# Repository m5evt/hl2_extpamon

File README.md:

# hl2_extpamon

## Overview

Power amplifier instrumentation board designed to couple to the Hermes-Lite2 SDR. 

The firmware/hardware is designed to couple to an LM35 temperature sensor.

The hardware should cope with upto 8 A of current to a power amplifer. However, at present the current is scaled to a full scale of 5 A. This can be changed in [hl2_extpamon.h](https://github.com/m5evt/hl2_extpamon/blob/main/firmware/hl2_extpamon.h). Other parameters such as automatic temperature turn on for the fan can be configured here.

The module uses an ATTINY414 device with an i2c address of 0x2A. 

## Reading data from device

Data can be read from the device over i2c by send the first data frame as 0x01.

For example, to read temperature and current from the device send:

```
07AA0100
```

This will return a 16 bit number comprised of the following bytes:

| Byte 3  | Byte 2 | Byte 1  | Byte 0 |
| ----------- | ----------- |----------- | ----------- |
| Device status      | PORTA status       |Current      | Temperature |

Temperature = e.g. 26 is 26 deg C

Current is scaled to a maximum current of 5 A represented in 255 bits. A return value of 128 = (128 / 255) * 5 = 2.51 A.

PORTA status corresponds to:

| Bit | Description |
|----------- | ----------- |
| 0 | Reserved |
| 1 | HL2 CN8 control |
| 2 | Enable PA power |
| 3 | FAN 1 |
| 4 | FAN 2 |
| 5 | N/a
| 6 | N/a
| 7 | Reserved |

Device status correspod to:

| Bit | Description |
|----------- | ----------- |
| 0 | Sampling ADC5 |
| 1 | Sampling ADC6 |

## Writing data to device

PORTA I/O can be set/clear by writing to address 0x02 in the device. For example, to enable the PA and turn on the fans send:

```
06AA021E
```

## Programming the ATTINY414

To program, the Makefile uses [pymcuprog](https://github.com/microchip-pic-avr-tools/pymcuprog) and UPDI. This does not require any specialist tools other than a TTL USB adapter and a resistor. See [here](https://github.com/mraardvark/pyupdi).

To program the device, from a command line run:
```
make clean && make erase && make program
```

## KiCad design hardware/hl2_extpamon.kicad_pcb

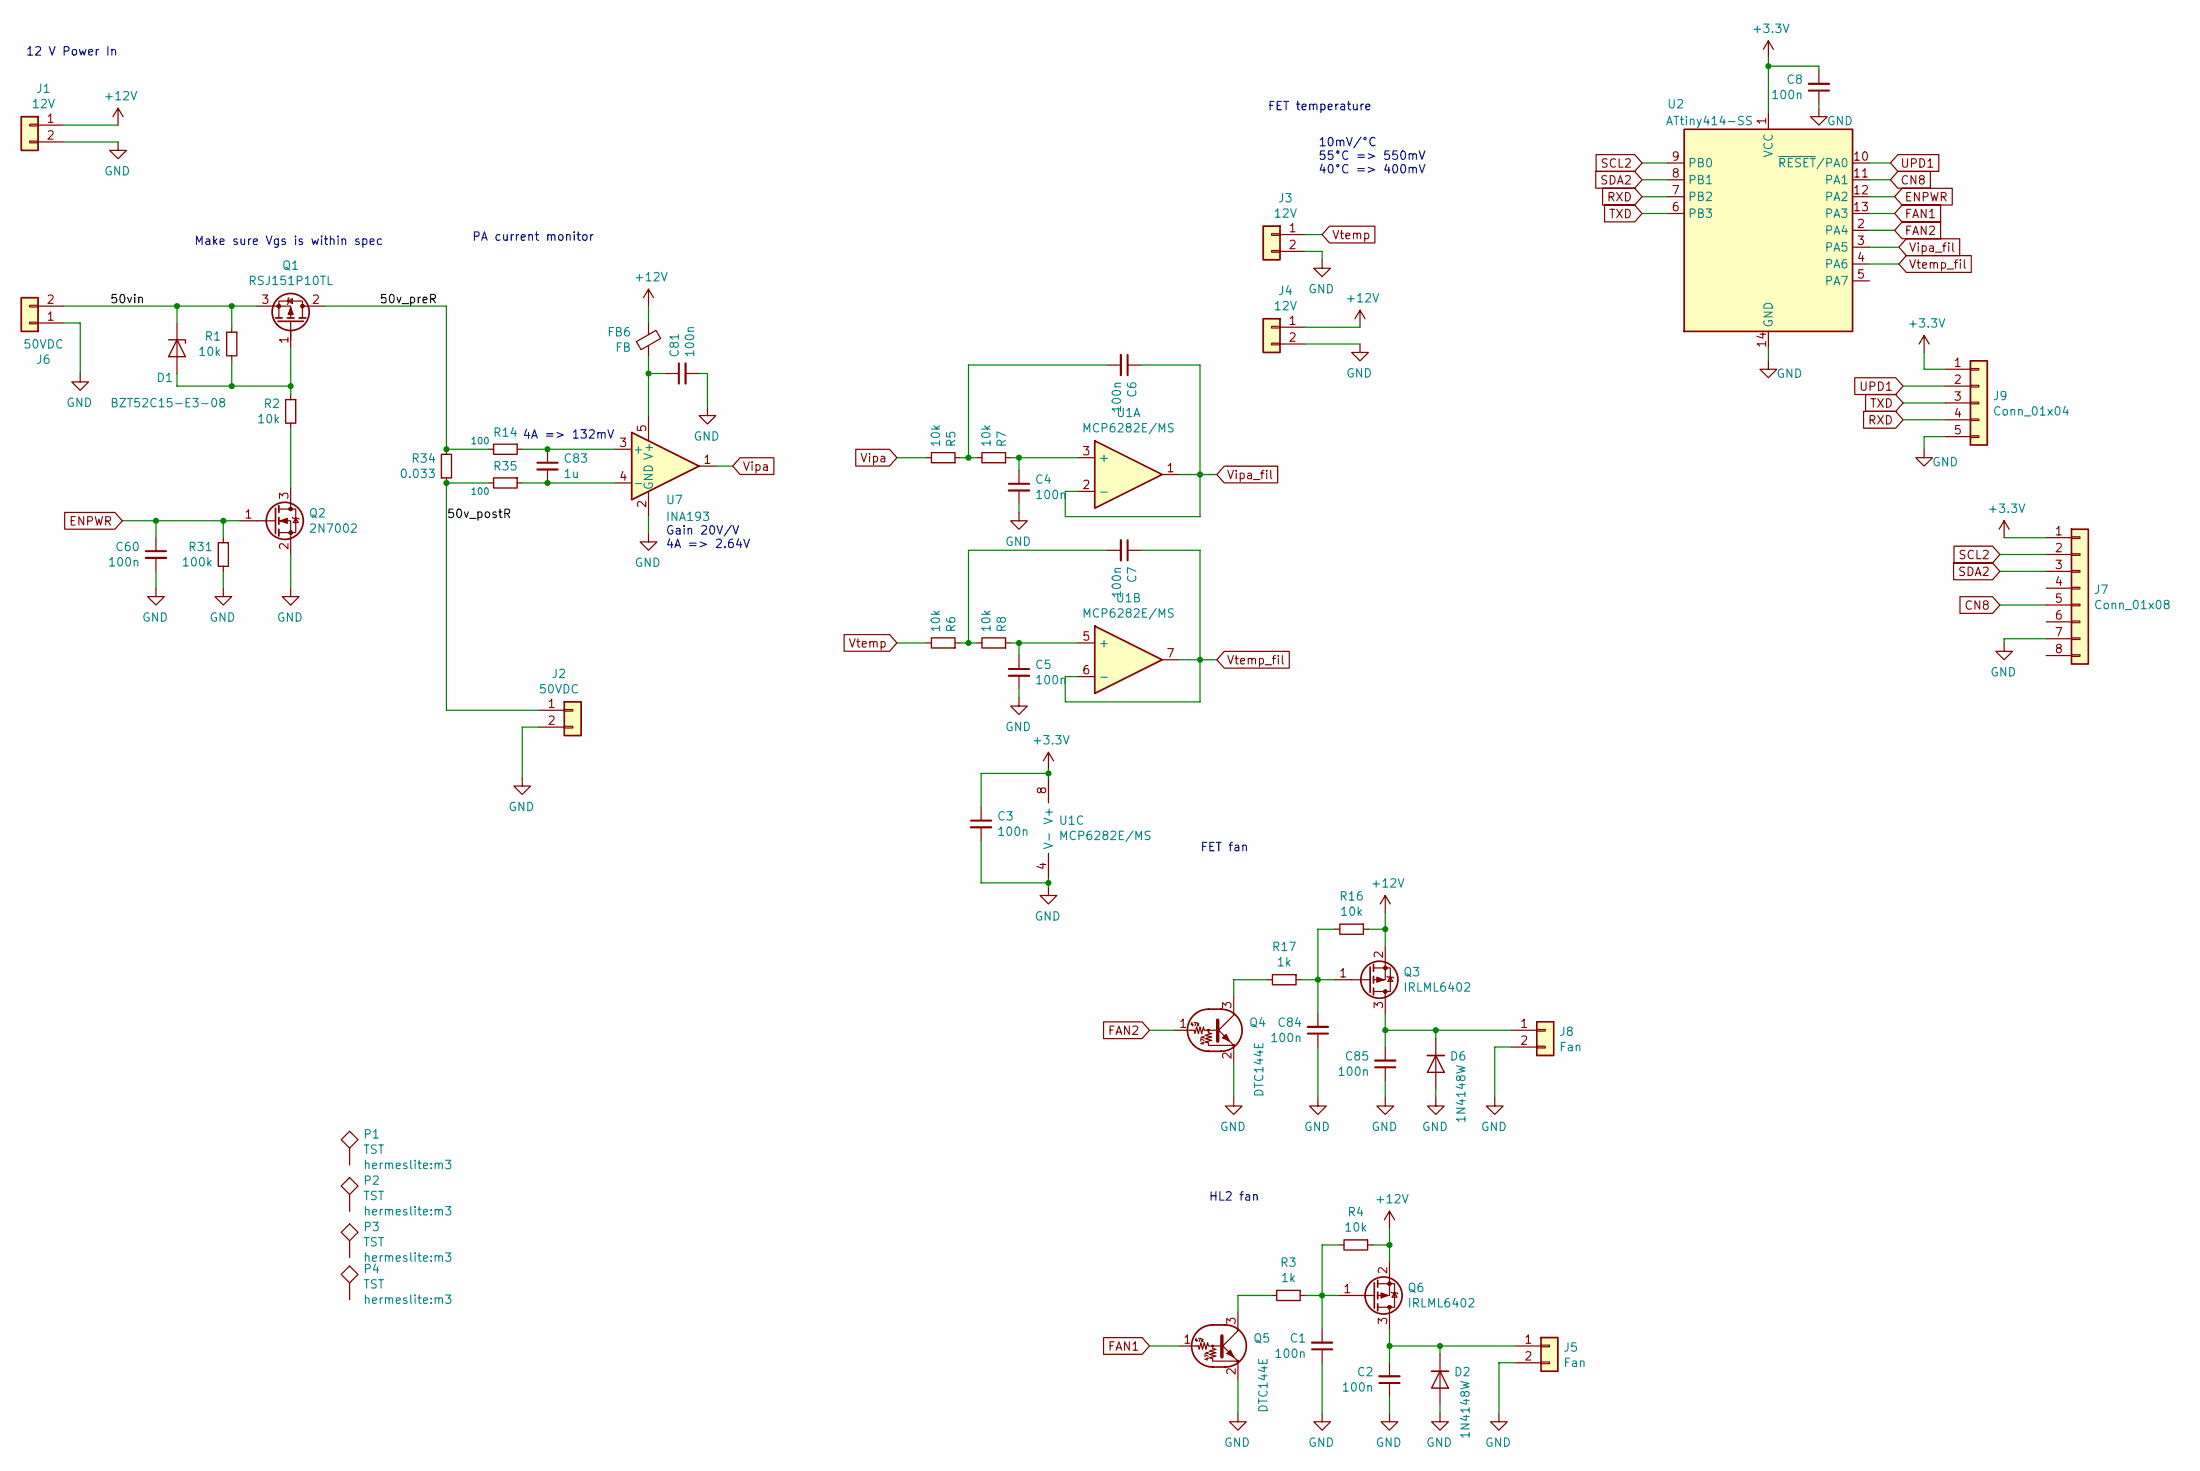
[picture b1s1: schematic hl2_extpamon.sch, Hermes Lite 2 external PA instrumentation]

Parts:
C1, C2, C3, C4, C5, C6, C7, C8, C60, C81, C84, C85: 100n; C_0603_1608Metric_Pad1.08x0.95mm_HandSolder
C83: 1u; C_0603_1608Metric_Pad1.08x0.95mm_HandSolder
D1: BZT52C15-E3-08; D_SOD-123
D2, D6: 1N4148W; D_SOD-123
FB6: FB; L_0805_2012Metric
J1, J3, J4: 12V; TerminalBlock_Phoenix_PT-1,5-2-3.5-H_1x02_P3.50mm_Horizontal
J2, J6: 50VDC; TerminalBlock_Phoenix_PT-1,5-2-5.0-H_1x02_P5.00mm_Horizontal
J5, J8: Fan; JST_XH_B2B-XH-A_1x02_P2.50mm_Vertical
J7: Conn_01x08; PinHeader_1x08_P2.54mm_Vertical
J9: Conn_01x04; PinHeader_1x05_P2.54mm_Vertical
P1, P2, P3, P4: TST; m3
Q1: RSJ151P10TL; TO-263-3_TabPin2
Q2: 2N7002; SOT-23
Q3, Q6: IRLML6402; SOT-23
Q4, Q5: DTC144E; SOT-23
R1, R2, R4, R5, R6, R7, R8, R16: 10k; R_0603_1608Metric_Pad0.98x0.95mm_HandSolder
R3, R17: 1k; R_0603_1608Metric_Pad0.98x0.95mm_HandSolder
R14, R35: 100; R_0603_1608Metric_Pad0.98x0.95mm_HandSolder
R31: 100k; R_0603_1608Metric_Pad0.98x0.95mm_HandSolder
R34: 0.033; rsense_1206wide
U1: MCP6282E/MS; MSOP-8_3x3mm_P0.65mm
U2: ATtiny414-SS; SOIC-14_3.9x8.7mm_P1.27mm
U7: INA193; SOT-23-5

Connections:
+3V3: C3.1, C8.2, J7.1, J9.1, U1.8 (V+), U2.1 (VCC)
+12V: FB6.2, J1.1, J4.1, Q3.2 (S), Q6.2 (S), R4.1, R16.1
/50v_postR: J2.1, R34.1, R35.2
/50v_preR: Q1.2 (D), R14.2, R34.2
/50vin: D1.1 (K), J6.2, Q1.3 (S), R1.1
CN8: J7.5, U2.11 (PA1)
ENPWR: C60.1, Q2.1 (G), R31.1, U2.12 (PA2)
FAN1: Q5.1 (B), U2.13 (PA3)
FAN2: Q4.1 (B), U2.2 (PA4)
GND: C1.1, C2.1, C3.2, C4.2, C5.2, C8.1, C60.2, C81.2, C84.1, C85.1, D2.2 (A), D6.2 (A), J1.2, J2.2, J3.2, J4.2, J5.2, J6.1, J7.7, J8.2, J9.5, Q2.2 (S), Q4.2 (E), Q5.2 (E), R31.2, U1.4 (V-), U2.14 (GND), U7.2 (GND)
unnamed: C1.2, Q6.1 (G), R3.1, R4.2
unnamed: C2.2, D2.1 (K), J5.1, Q6.3 (D)
unnamed: C4.1, R7.1, U1.3 (+)
unnamed: C5.1, R8.1, U1.5 (+)
unnamed: C6.2, R5.1, R7.2
unnamed: C7.2, R6.1, R8.2
unnamed: C81.1, FB6.1, U7.5 (V+)
unnamed: C83.1, R14.1, U7.3 (+)
unnamed: C83.2, R35.1, U7.4 (-)
unnamed: C84.2, Q3.1 (G), R16.2, R17.1
unnamed: C85.2, D6.1 (K), J8.1, Q3.3 (D)
unnamed: D1.2 (A), Q1.1 (G), R1.2, R2.1
unnamed: Q2.3 (D), R2.2
unnamed: Q4.3 (C), R17.2
unnamed: Q5.3 (C), R3.2
RXD: J9.4, U2.7 (PB2)
SCL2: J7.2, U2.9 (PB0)
SDA2: J7.3, U2.8 (PB1)
TXD: J9.3, U2.6 (PB3)
UPD1: J9.2, U2.10 (~RESET~/PA0)
Vipa: R5.2, U7.1
Vipa_fil: C6.1, U1.1, U1.2 (-), U2.3 (PA5)
Vtemp: J3.1, R6.2
Vtemp_fil: C7.1, U1.6 (-), U1.7, U2.4 (PA6)

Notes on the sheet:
10mV/°C 55°C => 550mV 40°C => 400mV
4A => 132mV
Gain 20V/V 4A => 2.64V
PA current monitor
FET temperature
FET fan
HL2 fan
Make sure Vgs is within spec
12 V Power In

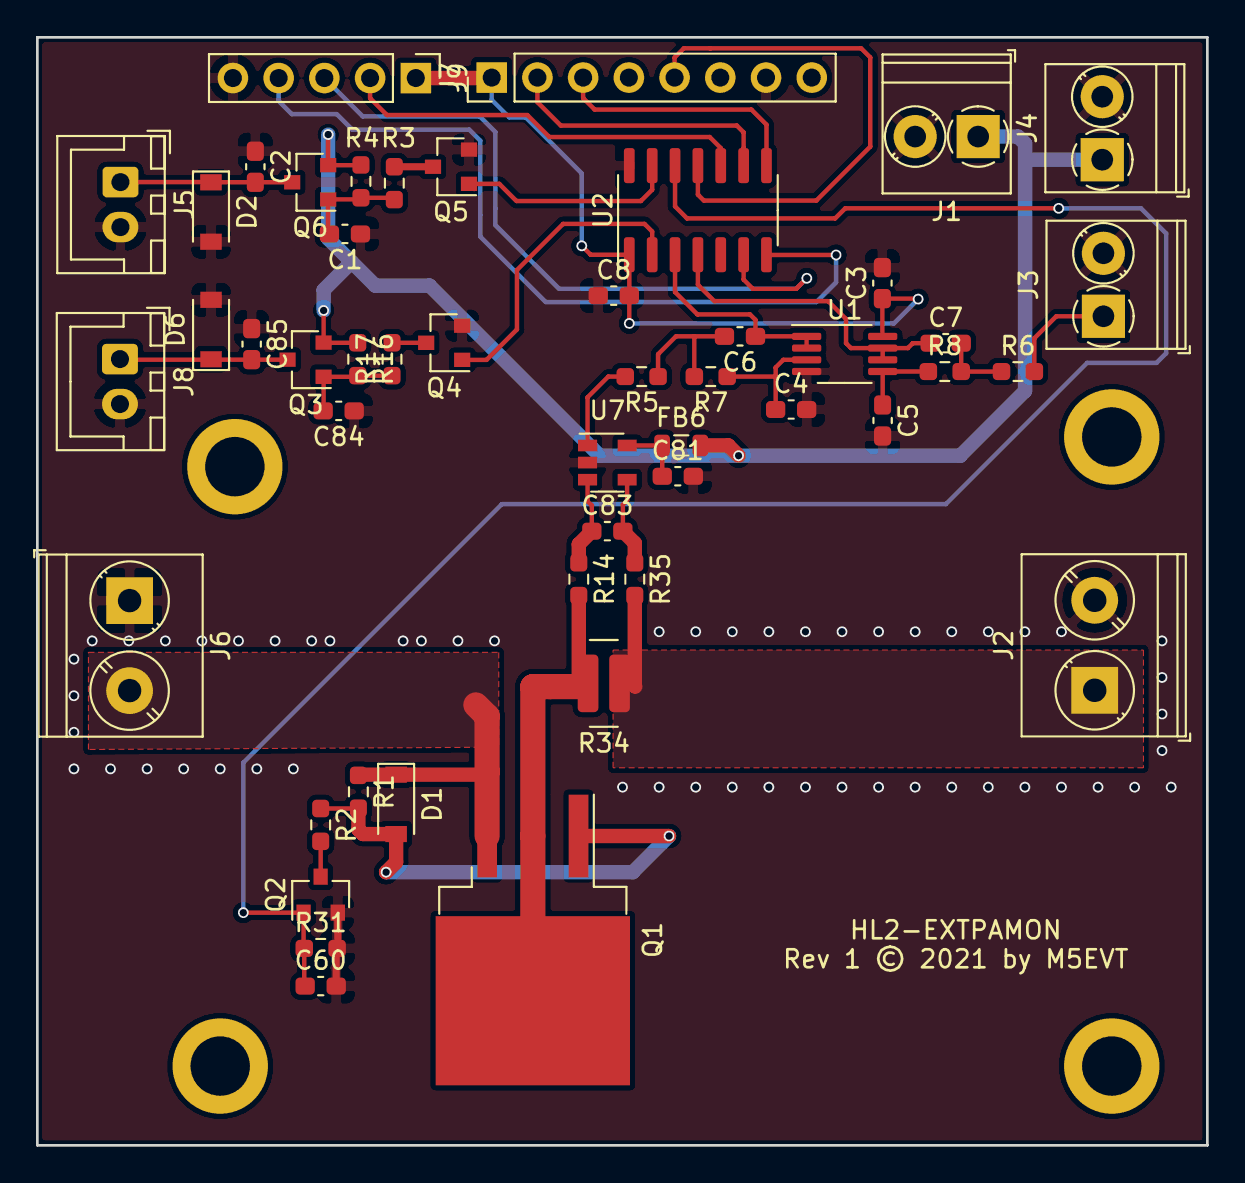
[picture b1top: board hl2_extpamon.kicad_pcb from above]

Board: 2 copper layers, 65.0 x 61.6 mm, 53 parts (0 on the bottom side), 34 nets.

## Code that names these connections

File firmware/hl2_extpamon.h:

/*
 *
 * This software is covered by a modified MIT License, see paragraphs 4
 *
 * Copyright (c) 2021 m5evt 
 *
 * 1. Permission is hereby granted, free of charge, to any person obtaining a copy
 * of this software and associated documentation files (the "Software"), to deal
 * in the Software without restriction, including without limitation the rights
 * to use, copy, modify, merge, publish, distribute, sublicense, and/or sell
 * copies of the Software, and to permit persons to whom the Software is
 * furnished to do so, subject to the following conditions:
 *
 * 2. The above copyright notice and this permission notice shall be included in all
 * copies or substantial portions of the Software.
 *
 * 3. THE SOFTWARE IS PROVIDED "AS IS", WITHOUT WARRANTY OF ANY KIND, EXPRESS OR
 * IMPLIED, INCLUDING BUT NOT LIMITED TO THE WARRANTIES OF MERCHANTABILITY,
 * FITNESS FOR A PARTICULAR PURPOSE AND NONINFRINGEMENT. IN NO EVENT SHALL THE
 * AUTHORS OR COPYRIGHT HOLDERS BE LIABLE FOR ANY CLAIM, DAMAGES OR OTHER
 * LIABILITY, WHETHER IN AN ACTION OF CONTRACT, TORT OR OTHERWISE, ARISING FROM,
 * OUT OF OR IN CONNECTION WITH THE SOFTWARE OR THE USE OR OTHER DEALINGS IN THE
 * SOFTWARE.
 *
 * 4. Parts of this software are adapted from Microchip sample code.
 * Additional license restrictions from Microchip may apply.
 */

// i2c memory map - data to send to HL2
#define FLAGS_STATUS       0x00 
#define MRF101_STATUS      0x01
// i2c memory map - config sent by HL2
#define SET_CFG            0x02
#define SET_CURRENT_TRIP   0x03
#define SET_TEMP_TRIP      0x04
// Outputs
#define IOPORT             PORTA_OUT
#define CN8                SBIT(PORTA_OUT, 1) 
#define ENPWR              SBIT(PORTA_OUT, 2) 
#define FAN1               SBIT(PORTA_OUT, 3) 
#define FAN2               SBIT(PORTA_OUT, 4) 
// Inputs
#define VIPA_FIL           SBIT(PORT_IN, 5) 
#define VTEMP_FIL          SBIT(PORT_IN, 6) 
// ADC channels
#define CURRENT            0x05
#define TEMPERATURE        0x06

//#define STATUSFLAGS_M      0b00011110
#define ADCSAMPLE_M          0b00000001
#define DO_ADC_M             0b00000010 
//#define FAN2_M             0b00000100
//#define CN8_M              0b00001000
//#define ENPWR_M            0b00010000

#define FAN_TEMP_THRESHOLD 29
#define CURRENT_SENSE_R 0.033
#define CURRENT_FULL_SCALE 5

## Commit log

2021-10-09 add schem
2021-10-10 licence in title of src
2021-10-10 Properly fix read/write i2c
2021-10-10 change current and temp scaling
2021-10-12 Code tidy up
2021-10-12 Fix current sampling
2021-10-27 Upload schematic, PCB and BoM
2021-10-27 Readme update

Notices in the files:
hardware/hl2_extpamon.kicad_pcb:
Rev 1 © 2021 by M5EVT
